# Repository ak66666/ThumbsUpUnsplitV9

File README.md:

# ThumbsUp! v9 ProMicro-Compatible MCU, Kailh Choc Switches

Multilevel 44/46 Key Contoured Keyboard.
2- or 3-key Thumb Cluster.

* ProMicro pin-compatible MCUs: Atmega32U4, RP2040
* Nice!nano (oritinal and clones) with battery for the bluetooth connectivity, power switch is supposed to be used.
* Supports ProGlide Cirque touchpad.
* Hot swap sockets for switches.
* Compact key spacing (18x17), large MX-size caps won't fit.

Other pictures in Photos folder.

# Firmware

Please refer to this article:
https://thumbsupkeyboards.blogspot.com/2024/02/source-files-and-default-firmware.html

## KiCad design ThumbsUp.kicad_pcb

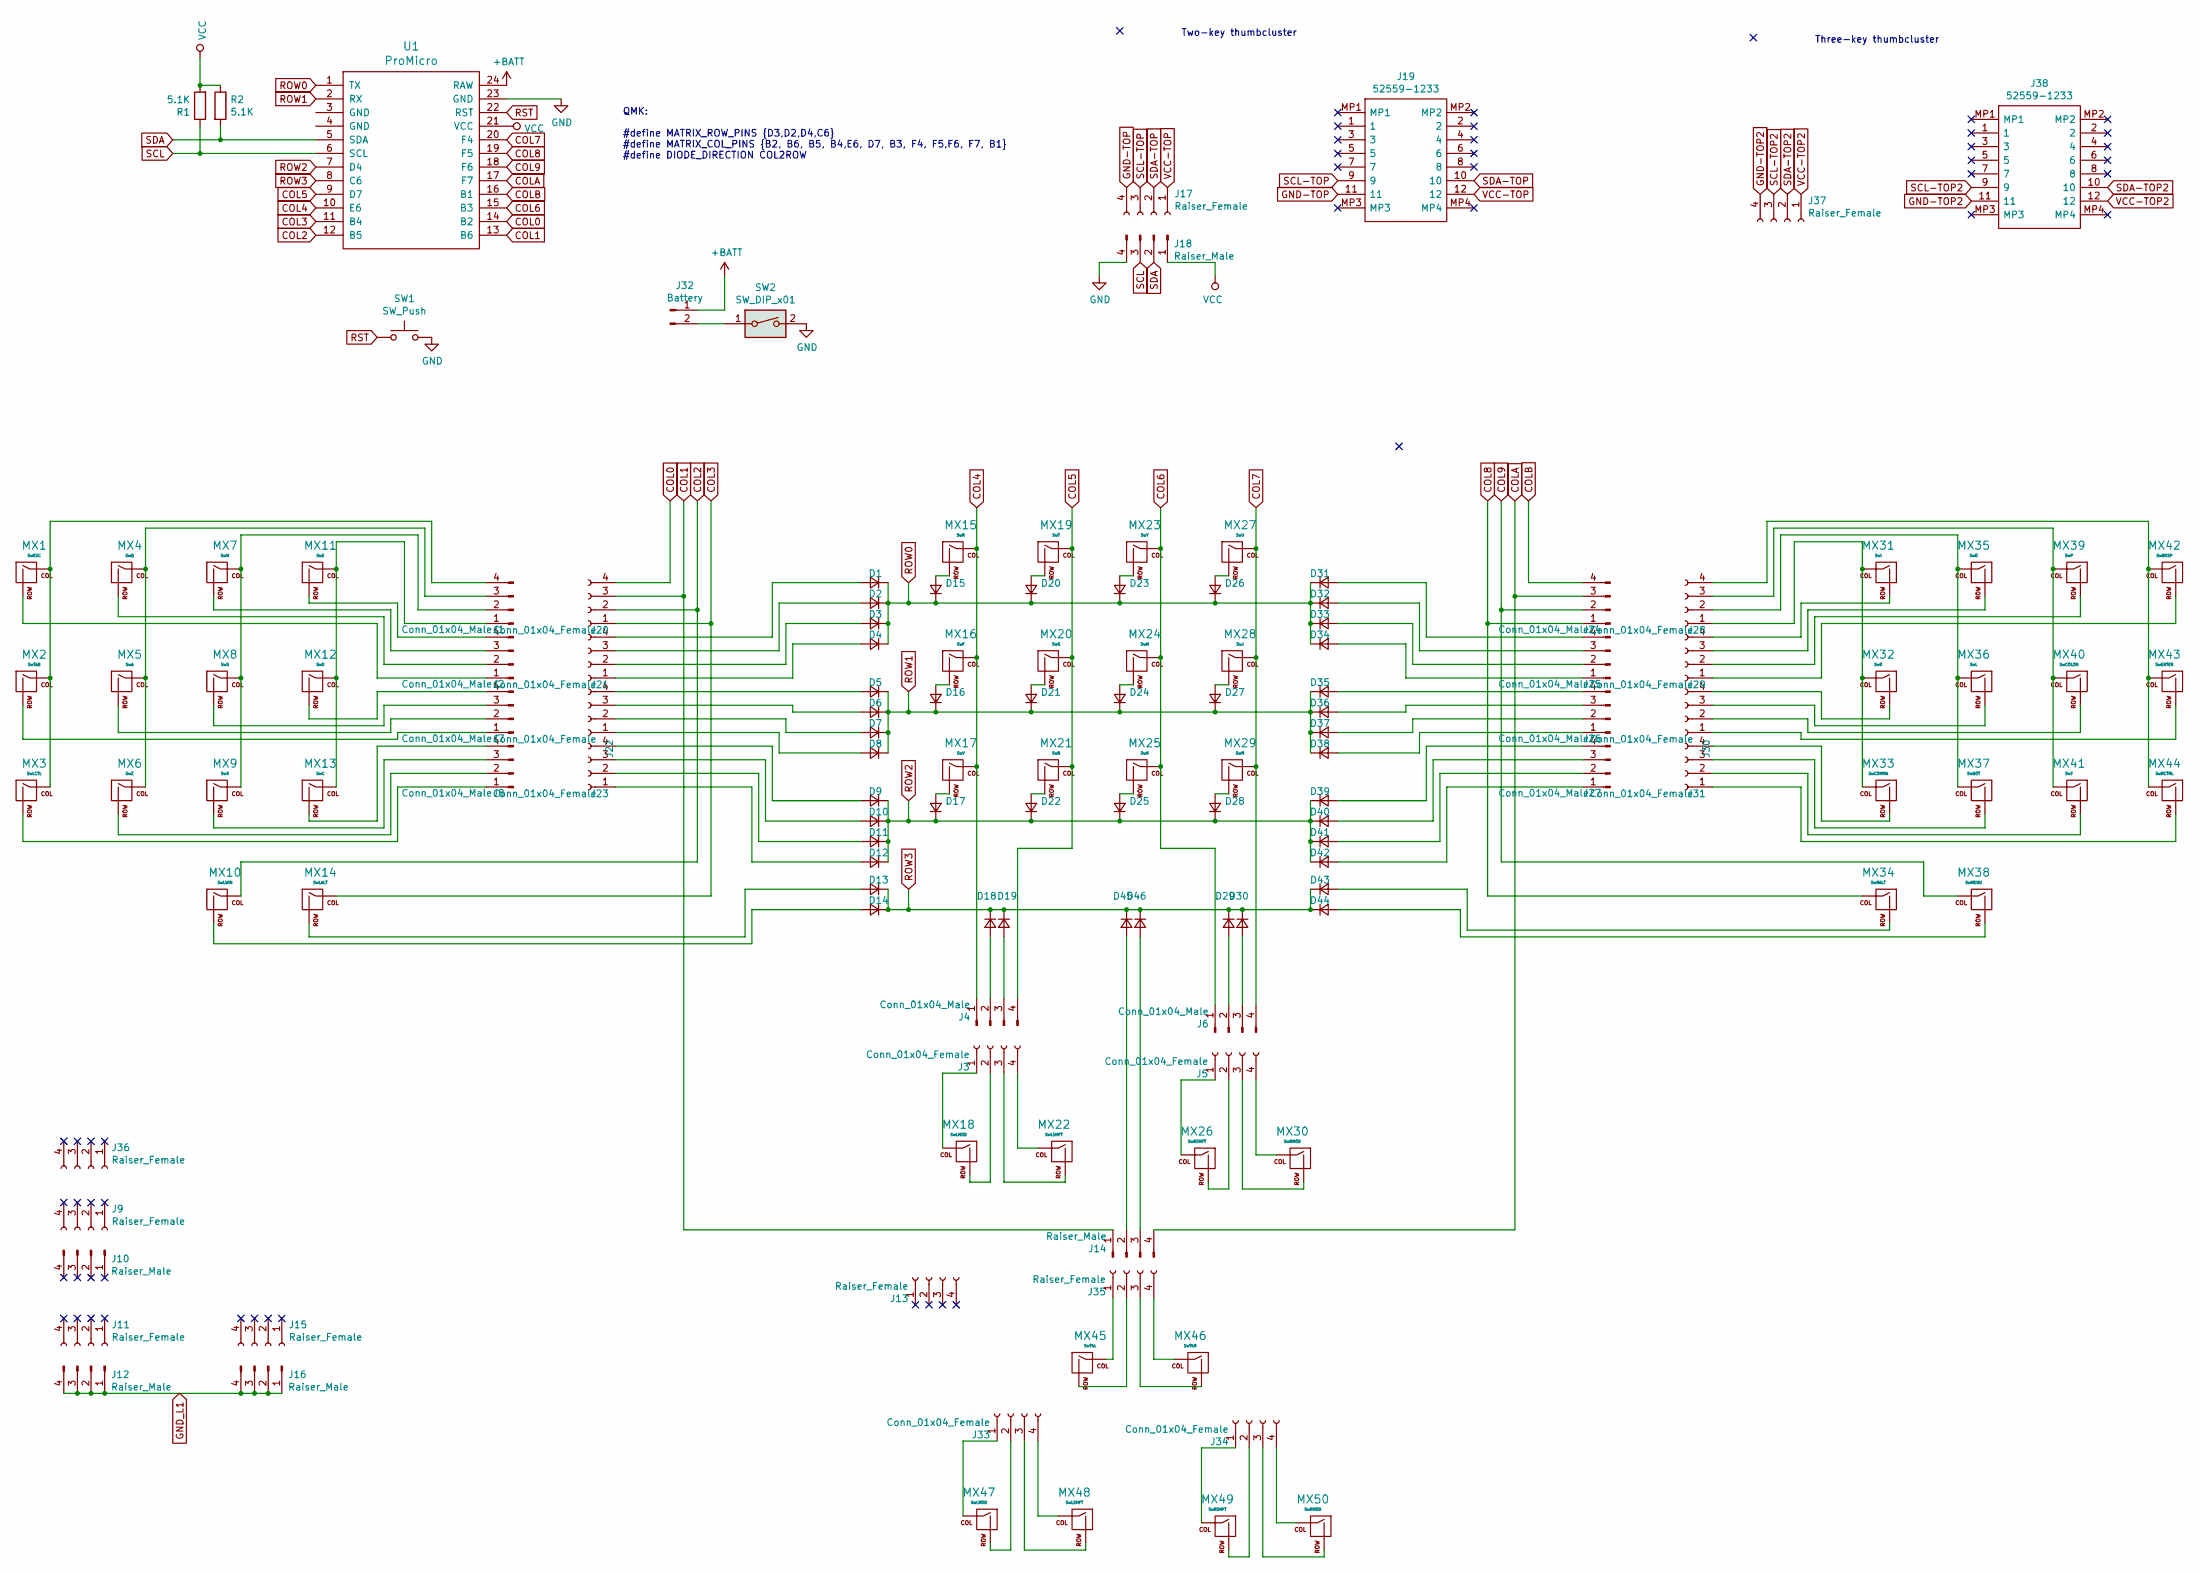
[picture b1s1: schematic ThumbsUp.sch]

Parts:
D1, D2, D3, D4, D5, D6, D7, D8, D9, D10, D11, D12, D13, D14, D15, D16, D17, D18, D19, D20, D21, D22, D23, D24, D25, D26, D27, D28, D29, D30, D31, D32, D33, D34, D35, D36, D37, D38, D39, D40, D41, D42, D43, D44, D45, D46: D_Small; D_SOD-123
J1, J2, J4, J6, J7, J8, J24, J25, J26, J27: Conn_01x04_Male; PinHeader_1x04_P2.54mm_Vertical
J3, J5, J20, J21, J22, J23, J28, J29, J30, J31, J33, J34: Conn_01x04_Female; PinSocket_1x04_P2.54mm_Vertical
J9, J11, J13, J15, J17, J35, J36, J37: Raiser_Female; PinSocket_1x04_P2.54mm_Vertical
J10, J12, J14, J16, J18: Raiser_Male; PinHeader_1x04_P2.54mm_Vertical
J19, J38: 52559-1233; 525591233; Mouser Part Number 538-52559-1233
J32: Battery; PinHeader_1x02_P2.54mm_Vertical
MX1: SwESC; Kailh_socket_PG1350_optional
MX2: SwTAB; Kailh_socket_PG1350_optional
MX3: SwLCTL; Kailh_socket_PG1350_optional
MX4: SwQ; Kailh_socket_PG1350_optional
MX5: SwA; Kailh_socket_PG1350_optional
MX6: SwZ; Kailh_socket_PG1350_optional
MX7: SwW; Kailh_socket_PG1350_optional
MX8: SwS; Kailh_socket_PG1350_optional
MX9: SwX; Kailh_socket_PG1350_optional
MX10: SwLWIN; Kailh_socket_PG1350_optional
MX11: SwE; Kailh_socket_PG1350_optional
MX12: SwD; Kailh_socket_PG1350_optional
MX13: SwC; Kailh_socket_PG1350_optional
MX14: SwLALT; Kailh_socket_PG1350_optional
MX15: SwR; Kailh_socket_PG1350_optional
MX16: SwF; Kailh_socket_PG1350_optional
MX17: SwV; Kailh_socket_PG1350_optional
MX18, MX47: SwLMOD; Kailh_socket_PG1350_optional
MX19: SwT; Kailh_socket_PG1350_optional
MX20: SwG; Kailh_socket_PG1350_optional
MX21: SwB; Kailh_socket_PG1350_optional
MX22, MX48: SwLSHFT; Kailh_socket_PG1350_optional
MX23: SwY; Kailh_socket_PG1350_optional
MX24: SwH; Kailh_socket_PG1350_optional
MX25: SwN; Kailh_socket_PG1350_optional
MX26, MX49: SwRSHFT; Kailh_socket_PG1350_optional
MX27: SwU; Kailh_socket_PG1350_optional
MX28: SwJ; Kailh_socket_PG1350_optional
MX29: SwM; Kailh_socket_PG1350_optional
MX30, MX50: SwRMOD; Kailh_socket_PG1350_optional
MX31: SwI; Kailh_socket_PG1350_optional
MX32: SwK; Kailh_socket_PG1350_optional
MX33: SwCOMMA; Kailh_socket_PG1350_optional
MX34: SwRALT; Kailh_socket_PG1350_optional
MX35: SwO; Kailh_socket_PG1350_optional
MX36: SwL; Kailh_socket_PG1350_optional
MX37: SwDOT; Kailh_socket_PG1350_optional
MX38: SwMENU; Kailh_socket_PG1350_optional
MX39: SwP; Kailh_socket_PG1350_optional
MX40: SwCOLON; Kailh_socket_PG1350_optional
MX41: Sw?; Kailh_socket_PG1350_optional
MX42: SwBKSP; Kailh_socket_PG1350_optional
MX43: SwENTER; Kailh_socket_PG1350_optional
MX44: SwRCTRL; Kailh_socket_PG1350_optional
MX45: SwThL; Kailh_socket_PG1350_optional
MX46: SwThR; Kailh_socket_PG1350_optional
R1, R2: 5.1K; R_0805_2012Metric
SW1: SW_Push; SKQG-1155865
SW2: SW_DIP_x01; 18252321
U1: ProMicro

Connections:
+BATT: J32.1, U1.24 (RAW)
COL0: J20.4, U1.14 (B2)
COL1: J14.1, J20.3, U1.13 (B6)
COL2: J20.2, MX10.1 (COL), U1.12 (B5)
COL3: J20.1, MX14.1 (COL), U1.11 (B4)
COL4: J4.1, MX15.1 (COL), MX16.1 (COL), MX17.1 (COL), U1.10 (E6)
COL5: J4.4, MX19.1 (COL), MX20.1 (COL), MX21.1 (COL), U1.9 (D7)
COL6: J6.1, MX23.1 (COL), MX24.1 (COL), MX25.1 (COL), U1.15 (B3)
COL7: J6.4, MX27.1 (COL), MX28.1 (COL), MX29.1 (COL), U1.20 (F4)
COL8: J24.1, MX34.1 (COL), U1.19 (F5)
COL9: J24.2, MX38.1 (COL), U1.18 (F6)
COLA: J14.4, J24.3, U1.17 (F7)
COLB: J24.4, U1.16 (B1)
GND: J18.4, SW1.2, SW2.2, U1.23 (GND)
GND-TOP: J17.4, J19.11
GND-TOP2: J37.4, J38.11
GND_L1: J12.1, J12.2, J12.3, J12.4, J16.1, J16.2, J16.3, J16.4
unnamed: D1.2 (A), J21.4
unnamed: D2.2 (A), J21.3
unnamed: D3.2 (A), J21.2
unnamed: D4.2 (A), J21.1
unnamed: D5.2 (A), J22.4
unnamed: D6.2 (A), J22.3
unnamed: D7.2 (A), J22.2
unnamed: D8.2 (A), J22.1
unnamed: D9.2 (A), J23.4
unnamed: D10.2 (A), J23.3
unnamed: D11.2 (A), J23.2
unnamed: D12.2 (A), J23.1
unnamed: D13.2 (A), MX14.2 (ROW)
unnamed: D14.2 (A), MX10.2 (ROW)
unnamed: D15.2 (A), MX15.2 (ROW)
unnamed: D16.2 (A), MX16.2 (ROW)
unnamed: D17.2 (A), MX17.2 (ROW)
unnamed: D18.2 (A), J4.2
unnamed: D19.2 (A), J4.3
unnamed: D20.2 (A), MX19.2 (ROW)
unnamed: D21.2 (A), MX20.2 (ROW)
unnamed: D22.2 (A), MX21.2 (ROW)
unnamed: D23.2 (A), MX23.2 (ROW)
unnamed: D24.2 (A), MX24.2 (ROW)
unnamed: D25.2 (A), MX25.2 (ROW)
unnamed: D26.2 (A), MX27.2 (ROW)
unnamed: D27.2 (A), MX28.2 (ROW)
unnamed: D28.2 (A), MX29.2 (ROW)
unnamed: D29.2 (A), J6.2
unnamed: D30.2 (A), J6.3
unnamed: D31.2 (A), J25.4
unnamed: D32.2 (A), J25.3
unnamed: D33.2 (A), J25.2
unnamed: D34.2 (A), J25.1
unnamed: D35.2 (A), J26.4
unnamed: D36.2 (A), J26.3
unnamed: D37.2 (A), J26.2
unnamed: D38.2 (A), J26.1
unnamed: D39.2 (A), J27.4
unnamed: D40.2 (A), J27.3
unnamed: D41.2 (A), J27.2
unnamed: D42.2 (A), J27.1
unnamed: D43.2 (A), MX34.2 (ROW)
unnamed: D44.2 (A), MX38.2 (ROW)
unnamed: D45.2 (A), J14.2
unnamed: D46.2 (A), J14.3
unnamed: J1.1, MX11.1 (COL), MX12.1 (COL), MX13.1 (COL)
unnamed: J1.2, MX7.1 (COL), MX8.1 (COL), MX9.1 (COL)
unnamed: J1.3, MX4.1 (COL), MX5.1 (COL), MX6.1 (COL)
unnamed: J1.4, MX1.1 (COL), MX2.1 (COL), MX3.1 (COL)
unnamed: J2.1, MX1.2 (ROW)
unnamed: J2.2, MX4.2 (ROW)
unnamed: J2.3, MX7.2 (ROW)
unnamed: J2.4, MX11.2 (ROW)
unnamed: J3.1, MX18.1 (COL)
unnamed: J3.2, MX18.2 (ROW)
unnamed: J3.3, MX22.2 (ROW)
unnamed: J3.4, MX22.1 (COL)
unnamed: J5.1, MX26.1 (COL)
unnamed: J5.2, MX26.2 (ROW)
unnamed: J5.3, MX30.2 (ROW)
unnamed: J5.4, MX30.1 (COL)
unnamed: J7.1, MX2.2 (ROW)
unnamed: J7.2, MX5.2 (ROW)
unnamed: J7.3, MX8.2 (ROW)
unnamed: J7.4, MX12.2 (ROW)
unnamed: J8.1, MX3.2 (ROW)
unnamed: J8.2, MX6.2 (ROW)
unnamed: J8.3, MX9.2 (ROW)
unnamed: J8.4, MX13.2 (ROW)
unnamed: J28.1, MX31.1 (COL), MX32.1 (COL), MX33.1 (COL)
unnamed: J28.2, MX35.1 (COL), MX36.1 (COL), MX37.1 (COL)
unnamed: J28.3, MX39.1 (COL), MX40.1 (COL), MX41.1 (COL)
unnamed: J28.4, MX42.1 (COL), MX43.1 (COL), MX44.1 (COL)
unnamed: J29.1, MX42.2 (ROW)
unnamed: J29.2, MX39.2 (ROW)
unnamed: J29.3, MX35.2 (ROW)
unnamed: J29.4, MX31.2 (ROW)
unnamed: J30.1, MX43.2 (ROW)
unnamed: J30.2, MX40.2 (ROW)
unnamed: J30.3, MX36.2 (ROW)
unnamed: J30.4, MX32.2 (ROW)
unnamed: J31.1, MX44.2 (ROW)
unnamed: J31.2, MX41.2 (ROW)
unnamed: J31.3, MX37.2 (ROW)
unnamed: J31.4, MX33.2 (ROW)
unnamed: J32.2, SW2.1
unnamed: J33.1, MX47.1 (COL)
unnamed: J33.2, MX47.2 (ROW)
unnamed: J33.3, MX48.2 (ROW)
unnamed: J33.4, MX48.1 (COL)
unnamed: J34.1, MX49.1 (COL)
unnamed: J34.2, MX49.2 (ROW)
unnamed: J34.3, MX50.2 (ROW)
unnamed: J34.4, MX50.1 (COL)
unnamed: J35.1, MX45.1 (COL)
unnamed: J35.2, MX45.2 (ROW)
unnamed: J35.3, MX46.2 (ROW)
unnamed: J35.4, MX46.1 (COL)
ROW0: D1.1 (K), D2.1 (K), D3.1 (K), D4.1 (K), D15.1 (K), D20.1 (K), D23.1 (K), D26.1 (K), D31.1 (K), D32.1 (K), D33.1 (K), D34.1 (K), U1.1 (TX)
ROW1: D5.1 (K), D6.1 (K), D7.1 (K), D8.1 (K), D16.1 (K), D21.1 (K), D24.1 (K), D27.1 (K), D35.1 (K), D36.1 (K), D37.1 (K), D38.1 (K), U1.2 (RX)
ROW2: D9.1 (K), D10.1 (K), D11.1 (K), D12.1 (K), D17.1 (K), D22.1 (K), D25.1 (K), D28.1 (K), D39.1 (K), D40.1 (K), D41.1 (K), D42.1 (K), U1.7 (D4)
ROW3: D13.1 (K), D14.1 (K), D18.1 (K), D19.1 (K), D29.1 (K), D30.1 (K), D43.1 (K), D44.1 (K), D45.1 (K), D46.1 (K), U1.8 (C6)
RST: SW1.1, U1.22 (RST)
SCL: J18.3, R1.1, U1.6 (SCL)
SCL-TOP: J17.3, J19.9
SCL-TOP2: J37.3, J38.9
SDA: J18.2, R2.2, U1.5 (SDA)
SDA-TOP: J17.2, J19.10
SDA-TOP2: J37.2, J38.10
VCC: J18.1, R1.2, R2.1, U1.21 (VCC)
VCC-TOP: J17.1, J19.12
VCC-TOP2: J37.1, J38.12

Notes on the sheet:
QMK: #define MATRIX_ROW_PINS {D3,D2,D4,C6} #define MATRIX_COL_PINS {B2, B6, B5, B4,E6, D7, B3, F4, F5,F6, F7, B1} #define DIODE_DIRECTION COL2ROW
Two-key thumbcluster
Three-key thumbcluster

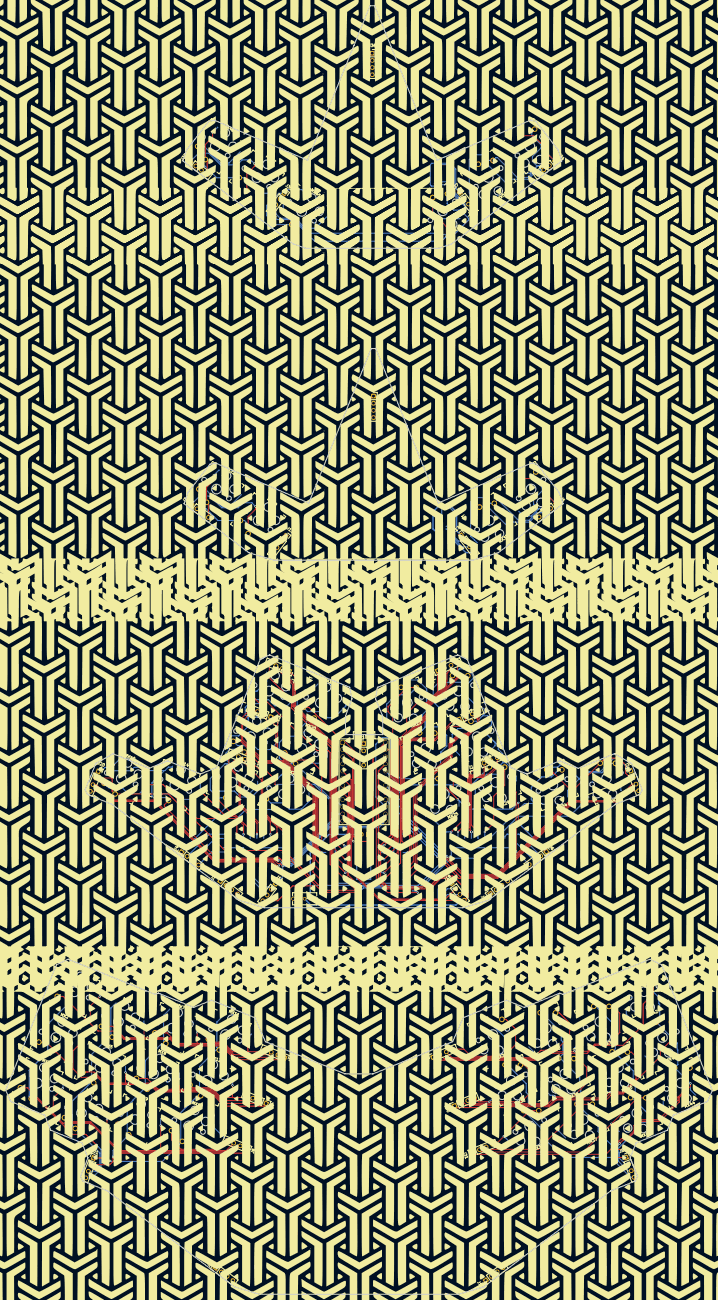
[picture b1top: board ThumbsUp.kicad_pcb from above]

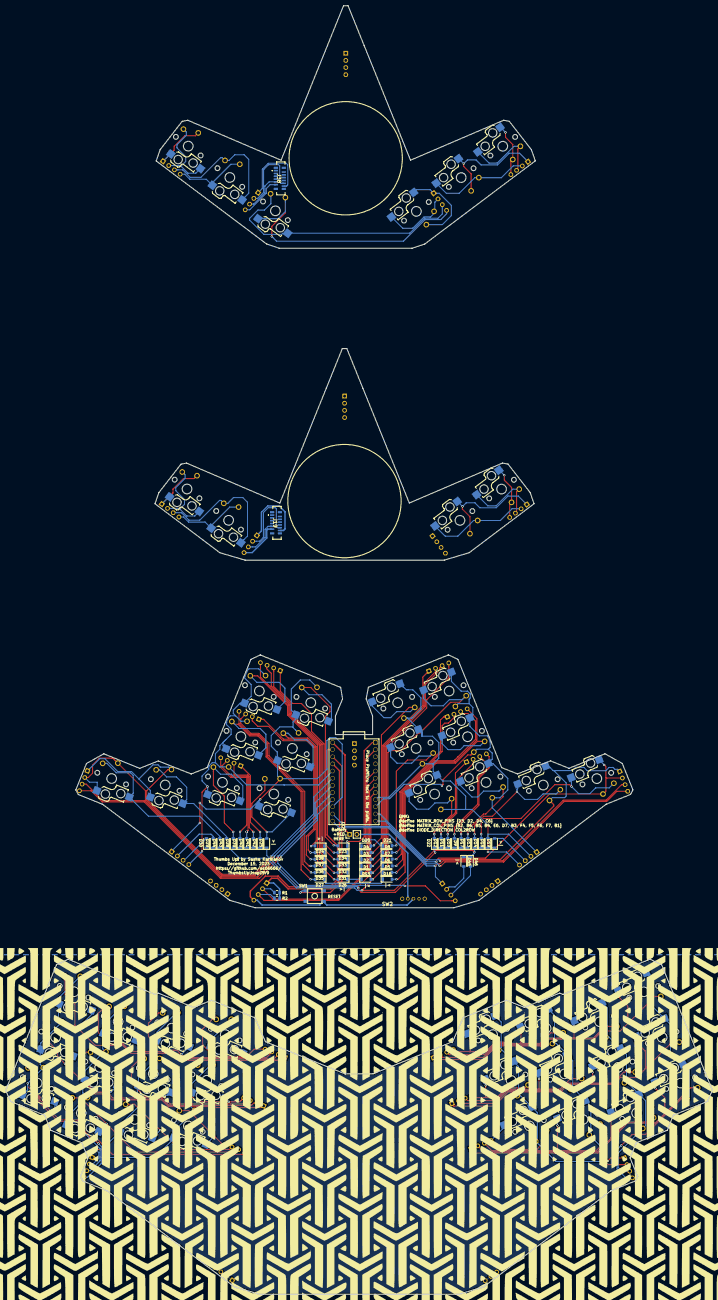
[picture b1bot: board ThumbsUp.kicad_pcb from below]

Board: 2 copper layers, 251.1 x 457.9 mm, 139 parts (52 on the bottom side), 130 nets.

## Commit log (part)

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2023-12-15 v9 Initial commit from v2.
2023-12-16 v9 Added the third key to the thumbcluster.
2023-12-27 v9 Redrew the lower PCB, added the silkscreens.
2024-01-01 v9 Gerbers generated
2025-02-27 ThumbsUp v9: Added photos, updated description.
